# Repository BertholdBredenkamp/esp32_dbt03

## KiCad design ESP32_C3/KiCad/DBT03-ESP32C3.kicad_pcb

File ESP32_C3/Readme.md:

# Hinweis - ESP32-C3 SuperMini DBT03 Modul

Ich habe die Programmquellen für die Arduino V2 IDE angepasst. Bei meinem Terminal musste die Abfrage für die Einstellungen auf die Taste 5 gelegt werden. Das erste Zeichen war immer die 1 die dann sofort beim Start die Einstellungen startete.

Bei den ersten Einstellungen dauert es ca. 20 Sekunden bis die Taste erkannt wird. Davor ist im Terminal ein kurzer Ton zu hören.

Die IP-Adresse des BTX Servers kann sowohl als Zahlenfolge wie auch als DNS Name eingegeben werden.

Die Verbindung zum BTX Terminal ist ein 7 poliges DIN Kabel. Bitte am Terminal schauen ob dort eine Buchse oder ein Stecker verbaut ist.

## Einstellungen

Die Einstellungen können nicht das Zeichen "#" enthalten, sie werden mit der Taste 5 innerhalb von 10 Sekunden nach dem Start der BTX Verbindung am  Terminal aufgerufen. Mit der Boot Taste lassen sich die Einstellungen komplett löschen (NVS löschen) wenn keine Terminalverbindung besteht.

## ESP WEB Tool

Mit dem ESP Webtool kann der ESP32_C3 SuperMini einfach programmiert werden. Leider geht es nur mit dem Chrome oder Edge Browser. 
Der Aufruf von : https://bertholdbredenkamp.github.io/esp32_dbt03//ESP32_C3/flash.html startet das Tool nach klick auf Connect wird der Serielle Port an dem das Modul angeschlossen ist abgefragt und dann startet die Übertragung.

## Hinweise

Das Layout basiert auf einem ESP32-C3 SuperMini Board. Bei meinem Modell musste ich die Sendeleistung verringern. Es gibt auch Empfehlungen eine Antenne zusätzlich aufzulöten. Bei anderen Ausführungen des ESP Moduls soll der Fehler nicht vorhanden sein.

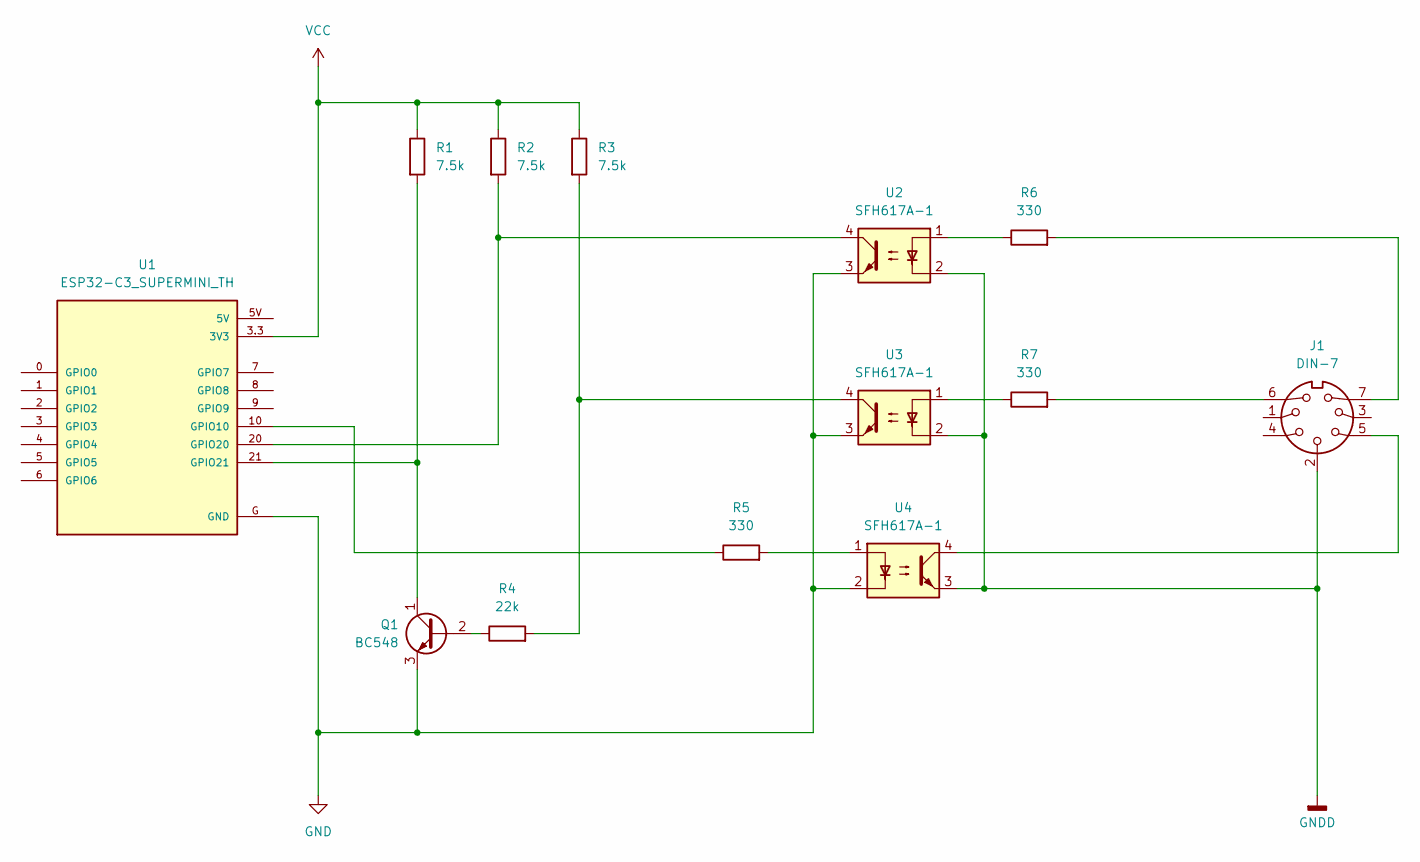
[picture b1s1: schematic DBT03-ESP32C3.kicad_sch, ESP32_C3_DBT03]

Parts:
J1: DIN-7; DIN_7_Buchse
Q1: BC548; TO-92_Inline
R1, R2, R3: 7.5k; R_Axial_DIN0207_L6.3mm_D2.5mm_P10.16mm_Horizontal
R4: 22k; R_Axial_DIN0207_L6.3mm_D2.5mm_P10.16mm_Horizontal
R5, R6, R7: 330; R_Axial_DIN0207_L6.3mm_D2.5mm_P10.16mm_Horizontal
U1: ESP32-C3_SUPERMINI_TH; MODULE_ESP32-C3_SUPERMINI_TH
U2, U3, U4: SFH617A-1; DIP-4_W7.62mm

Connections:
GND: Q1.3 (E), U1.G (GND), U2.3, U3.3, U4.2
GNDD: J1.2, U2.2, U3.2, U4.3
unnamed: J1.5, U4.4
unnamed: J1.6, R7.2
unnamed: J1.7, R6.2
unnamed: Q1.2 (B), R4.1
unnamed: Q1.1 (C), R1.2, U1.21 (GPIO21)
unnamed: R3.2, R4.2, U3.4
unnamed: R5.2, U4.1
unnamed: R6.1, U2.1
unnamed: R7.1, U3.1
unnamed: R5.1, U1.10 (GPIO10)
unnamed: R2.2, U1.20 (GPIO20), U2.4
VCC: R1.1, R2.1, R3.1, U1.3.3 (3V3)

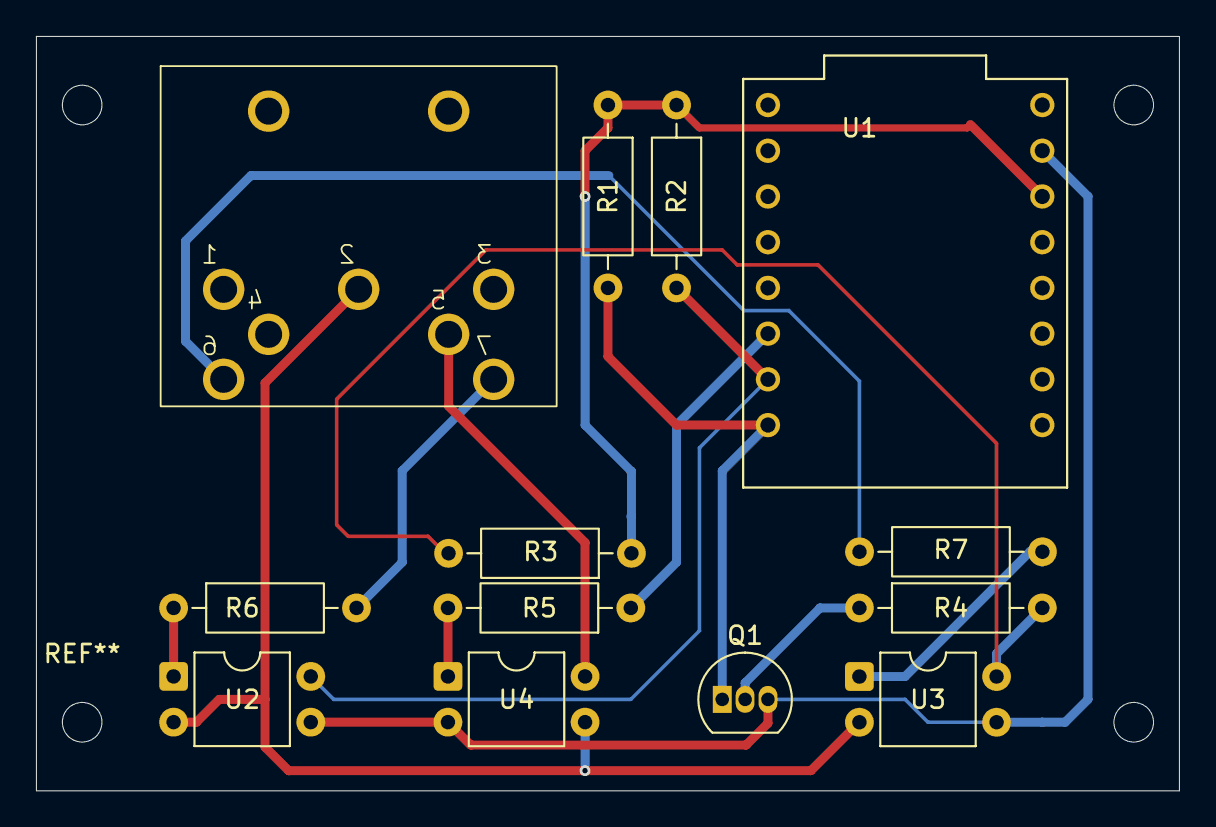
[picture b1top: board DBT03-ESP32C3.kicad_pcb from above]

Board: 2 copper layers, 63.5 x 41.9 mm, 13 parts (0 on the bottom side), 14 nets.

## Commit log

2025-11-08 Adding KiCad Schematic (#5)
    * Create ESP-DBT03.sch
    * Add KiCad schematic
    Adding The Schmatics as a Kicad File
    * Delete KiCad/ESP-DBT03.sch
2026-04-07 ESP32_C3 firmware und KiCad hinzugefügt
    Anpassung an Arduino und ESP32_C3
2026-04-09 Readme hinzugefügt
2026-04-10 NVS löschen
2026-04-14 Gehäuse STL hinzugefügt
    Gehäuse 3D Druck
2026-04-18 Anpassung HostName
    Erweiterung der Einstellungen um den Host Namen
2026-04-18 Dateien verschoben
2026-04-18 Schreibfehler
2026-04-18 Hostname hinzu
